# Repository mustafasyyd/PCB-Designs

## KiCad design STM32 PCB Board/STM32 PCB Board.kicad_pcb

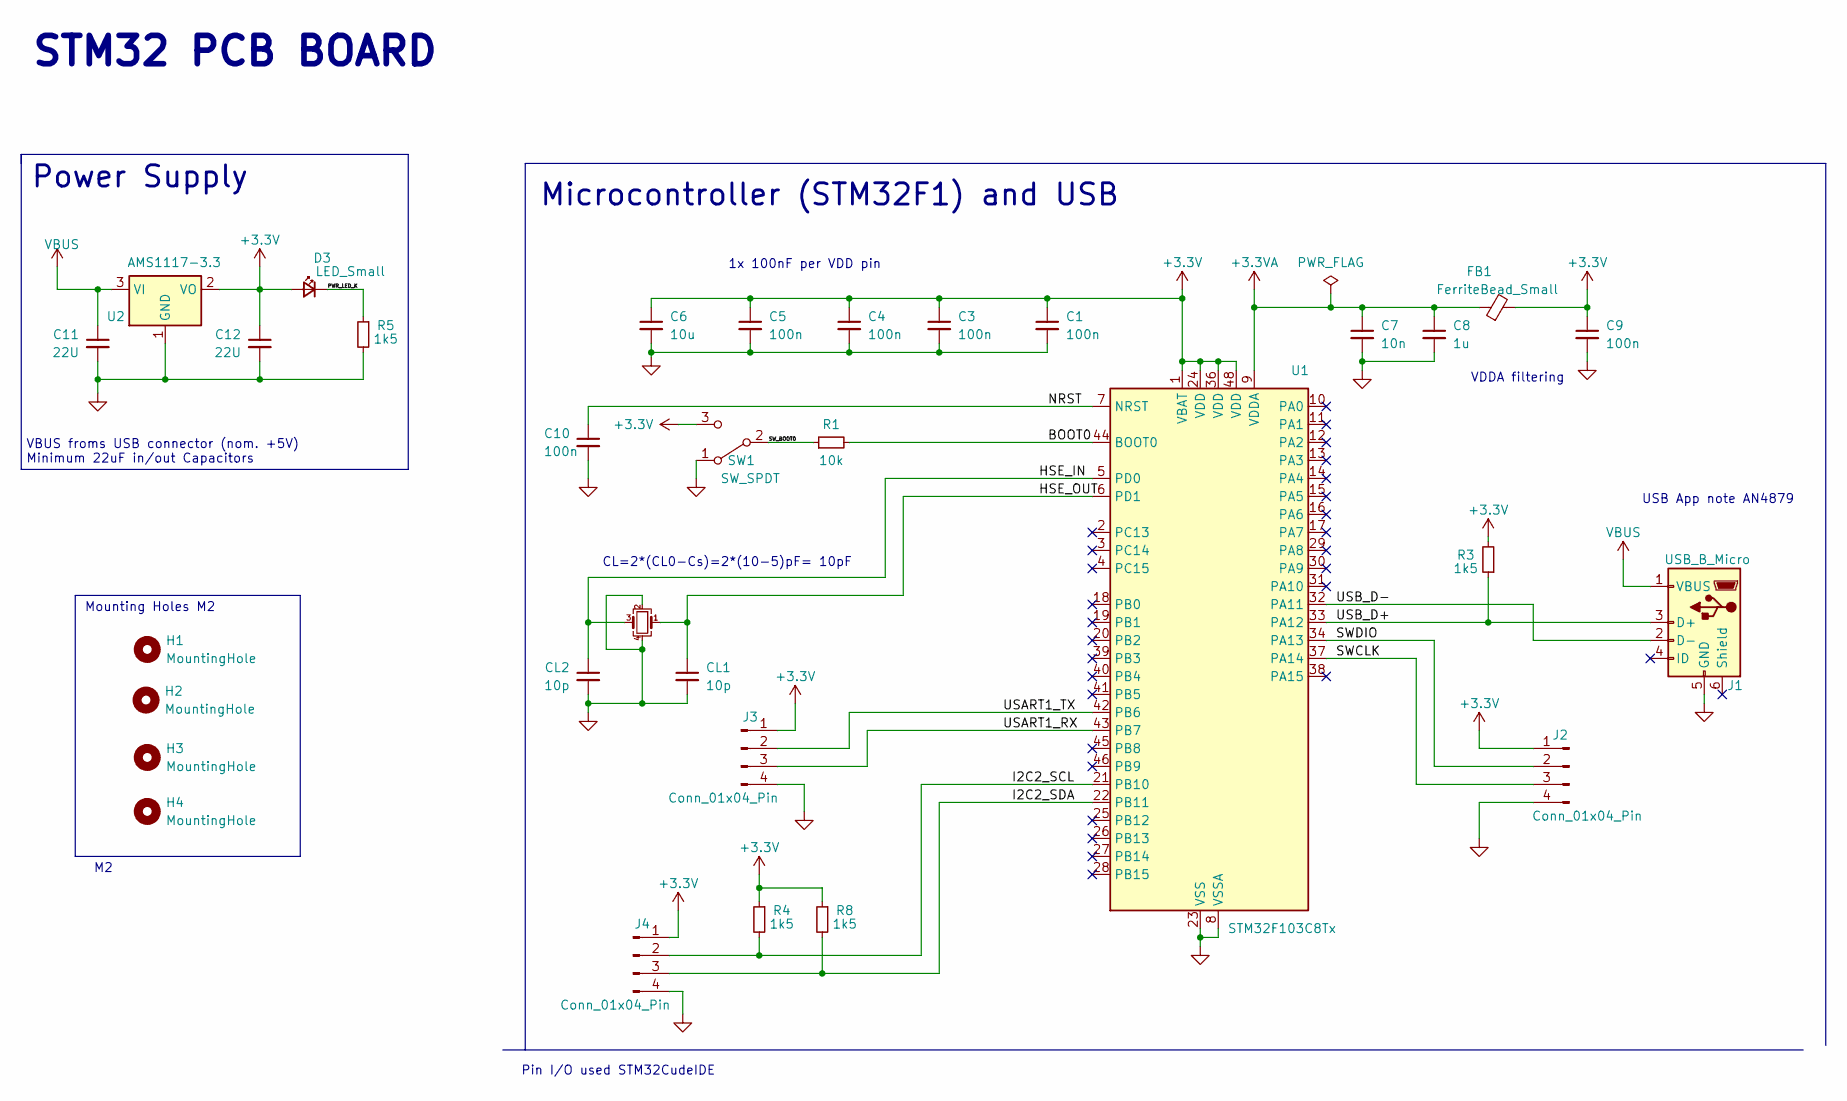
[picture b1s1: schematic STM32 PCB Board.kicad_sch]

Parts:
C1, C3, C4, C5, C9, C10: 100n; C_0201_0603Metric_Pad0.64x0.40mm_HandSolder
C6: 10u; C_0201_0603Metric_Pad0.64x0.40mm_HandSolder
C7: 10n; C_0201_0603Metric_Pad0.64x0.40mm_HandSolder
C8: 1u; C_0201_0603Metric_Pad0.64x0.40mm_HandSolder
C11, C12: 22U; C_0201_0603Metric_Pad0.64x0.40mm_HandSolder
CL1, CL2: 10p; C_0201_0603Metric_Pad0.64x0.40mm_HandSolder
D3: LED_Small; LED_0201_0603Metric_Pad0.64x0.40mm_HandSolder
FB1: FerriteBead_Small; LairdTech_28C0236-0JW-10
H1, H2, H3, H4: MountingHole; MountingHole_2.2mm_M2
J1: USB_B_Micro; USB_Micro-B_Wuerth_629105150521_CircularHoles
J2, J3, J4: Conn_01x04_Pin; PinHeader_1x04_P1.00mm_Vertical
R1: 10k; R_0402_1005Metric
R3, R4, R5, R8: 1k5; R_0402_1005Metric
SW1: SW_SPDT; SW_SPDT_PCM12
U1: STM32F103C8Tx; LQFP-48_7x7mm_P0.5mm
U2: AMS1117-3.3; SOT-223-3_TabPin2
Y3: 16MHz; Oscillator_SMD_Kyocera_KC2520Z-4Pin_2.5x2.0mm

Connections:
+3.3V: C1.1, C3.1, C4.1, C5.1, C6.1, C9.1, C12.1, D3.2 (A), FB1.2, J2.1, J3.1, J4.1, R3.2, R4.1, R8.1, SW1.3 (C), U1.1 (VBAT), U1.24 (VDD), U1.36 (VDD), U1.48 (VDD), U2.2 (VO)
+3.3VA: C7.1, C8.1, FB1.1, U1.9 (VDDA)
/BOOT0: R1.2, U1.44 (BOOT0)
/HSE_IN: CL2.1, U1.5 (PD0), Y3.3
/HSE_OUT: CL1.1, U1.6 (PD1), Y3.1
/I2C2_SCL: J4.2, R4.2, U1.21 (PB10)
/I2C2_SDA: J4.3, R8.2, U1.22 (PB11)
/NRST: C10.1, U1.7 (NRST)
/PWR_LED_K: D3.1 (K), R5.1
/SWCLK: J2.3, U1.37 (PA14)
/SWDIO: J2.2, U1.34 (PA13)
/SW_BOOT0: R1.1, SW1.2 (B)
/USART1_RX: J3.3, U1.43 (PB7)
/USART1_TX: J3.2, U1.42 (PB6)
/USB_D+: J1.3 (D+), R3.1, U1.33 (PA12)
/USB_D-: J1.2 (D-), U1.32 (PA11)
GND1: C1.2, C3.2, C4.2, C5.2, C6.2, C7.2, C8.2, C9.2, C10.2, C11.2, C12.2, CL1.2, CL2.2, J1.5 (GND), J2.4, J3.4, J4.4, R5.2, SW1.1 (A), U1.8 (VSSA), U1.23 (VSS), U1.35 (VSS), U1.47 (VSS), U2.1 (GND), Y3.2, Y3.4
VBUS: C11.1, J1.1 (VBUS), U2.3 (VI)

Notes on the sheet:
USB App note AN4879
CL=2*(CL0-Cs)=2*(10-5)pF= 10pF
1x 100nF per VDD pin
STM32 PCB BOARD
Mounting Holes M2
VBUS froms USB connector (nom. +5V) Minimum 22uF in/out Capacitors
Pin I/O used STM32CudeIDE
VDDA filtering
Microcontroller (STM32F1) and USB
Power Supply

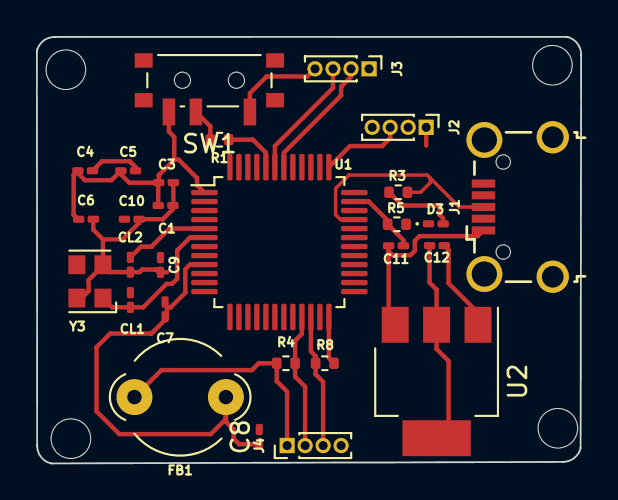
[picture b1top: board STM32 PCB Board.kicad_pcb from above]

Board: 2 copper layers, 30.2 x 23.7 mm, 32 parts (0 on the bottom side), 18 nets.

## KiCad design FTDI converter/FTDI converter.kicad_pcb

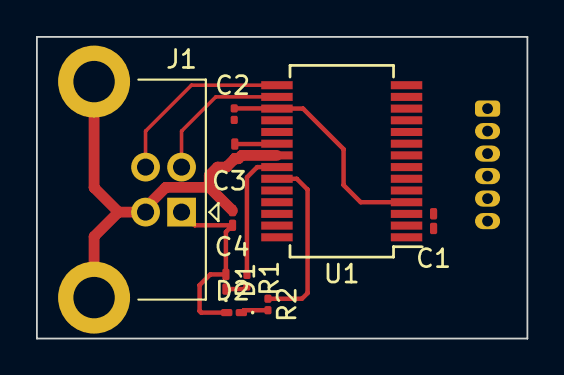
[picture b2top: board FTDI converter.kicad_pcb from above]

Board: 2 copper layers, 27.2 x 16.8 mm, 11 parts (1 on the bottom side), 12 nets.

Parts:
C1, C3: 100nF; C_0201_0603Metric_Pad0.64x0.40mm_HandSolder
C2: 100nF; C_0201_0603Metric
C4: 4.7uF; C_0201_0603Metric_Pad0.64x0.40mm_HandSolder
D1, D2: LED_0201_0603Metric_Pad0.64x0.40mm_HandSolder
J1: USB_B; USB_B_Lumberg_2411_02_Horizontal
J2: Conn_01x06_Pin; Hirose_DF13-06P-1.25DSA_1x06_P1.25mm_Vertical
R1, R2: 1k; R_0201_0603Metric
U1: FT232RL; SSOP-28_5.3x10.2mm_P0.65mm

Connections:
+3V3: C1.1, C2.1, J2.5, U1.4 (VCCIO), U1.17 (3V3OUT)
+5V: C3.1, C4.1, D1.2 (A), D2.2 (A), J1.1 (VBUS), J2.4, U1.20 (VCC)
/D+: J1.3 (D+), U1.15 (USBD+)
/D-: J1.2 (D-), U1.16 (USBD-)
/DTR: J2.1, U1.2 (DTR)
/RXD: J2.2, U1.5 (RXD)
/TXD: J2.3, U1.1 (TXD)
GND: C1.2, C2.2, C3.2, C4.2, J1.4 (GND), J1.5 (Shield), J2.6, U1.7 (GND), U1.18 (GND), U1.21 (GND), U1.25 (AGND), U1.26 (TEST)
unnamed: D1.1 (K), R1.2
unnamed: D2.1 (K), R2.2
unnamed: R2.1, U1.23 (CBUS0)
unnamed: R1.1, U1.22 (CBUS1)

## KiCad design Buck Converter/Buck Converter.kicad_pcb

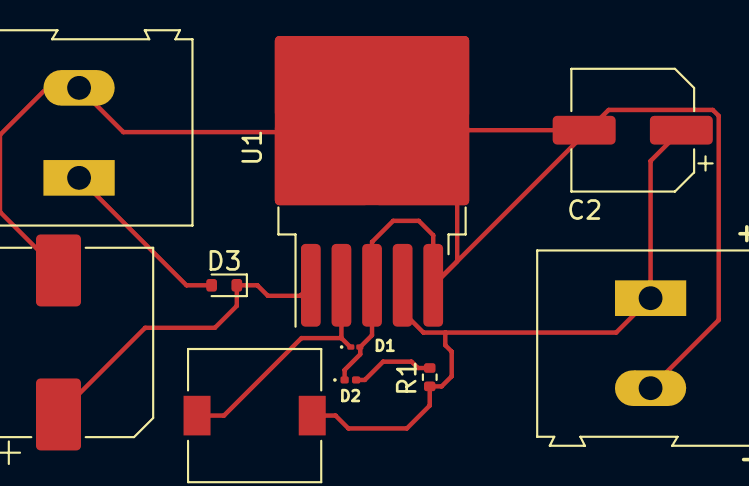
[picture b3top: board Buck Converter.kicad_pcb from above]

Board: 2 copper layers, 10 parts (0 on the bottom side), 6 nets.

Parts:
C1: 680uF; CP_Elec_10x10
C2: 220uF; CP_Elec_6.3x7.7
D1: 1N5822; D_01005_0402Metric
D2: LED_Small; LED_0201_0603Metric
D3: 1N914WT; D_SOD-523
J1: -Power In+; TerminalBlock_Altech_AK300-2_P5.00mm
J2: -Power Out+; TerminalBlock_Altech_AK300-2_P5.00mm
L1: 33uH; L_7.3x7.3_H3.5
R1: 1k5; R_0402_1005Metric
U1: LM2596S-5; TO-263-5_TabPin3

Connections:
+5V: C2.1, J2.1, L1.2, R1.1, U1.4 (FB)
GND: C1.2, C2.2, D1.2 (A), D2.1 (K), J1.2, J2.2, U1.3 (GND), U1.5 (~ON/OFF)
unnamed: D1.1 (K), L1.1, U1.2 (OUT)
unnamed: D2.2 (A), R1.2
unnamed: C1.1, D3.1 (K), U1.1 (VIN)
VDC: D3.2 (A), J1.1
